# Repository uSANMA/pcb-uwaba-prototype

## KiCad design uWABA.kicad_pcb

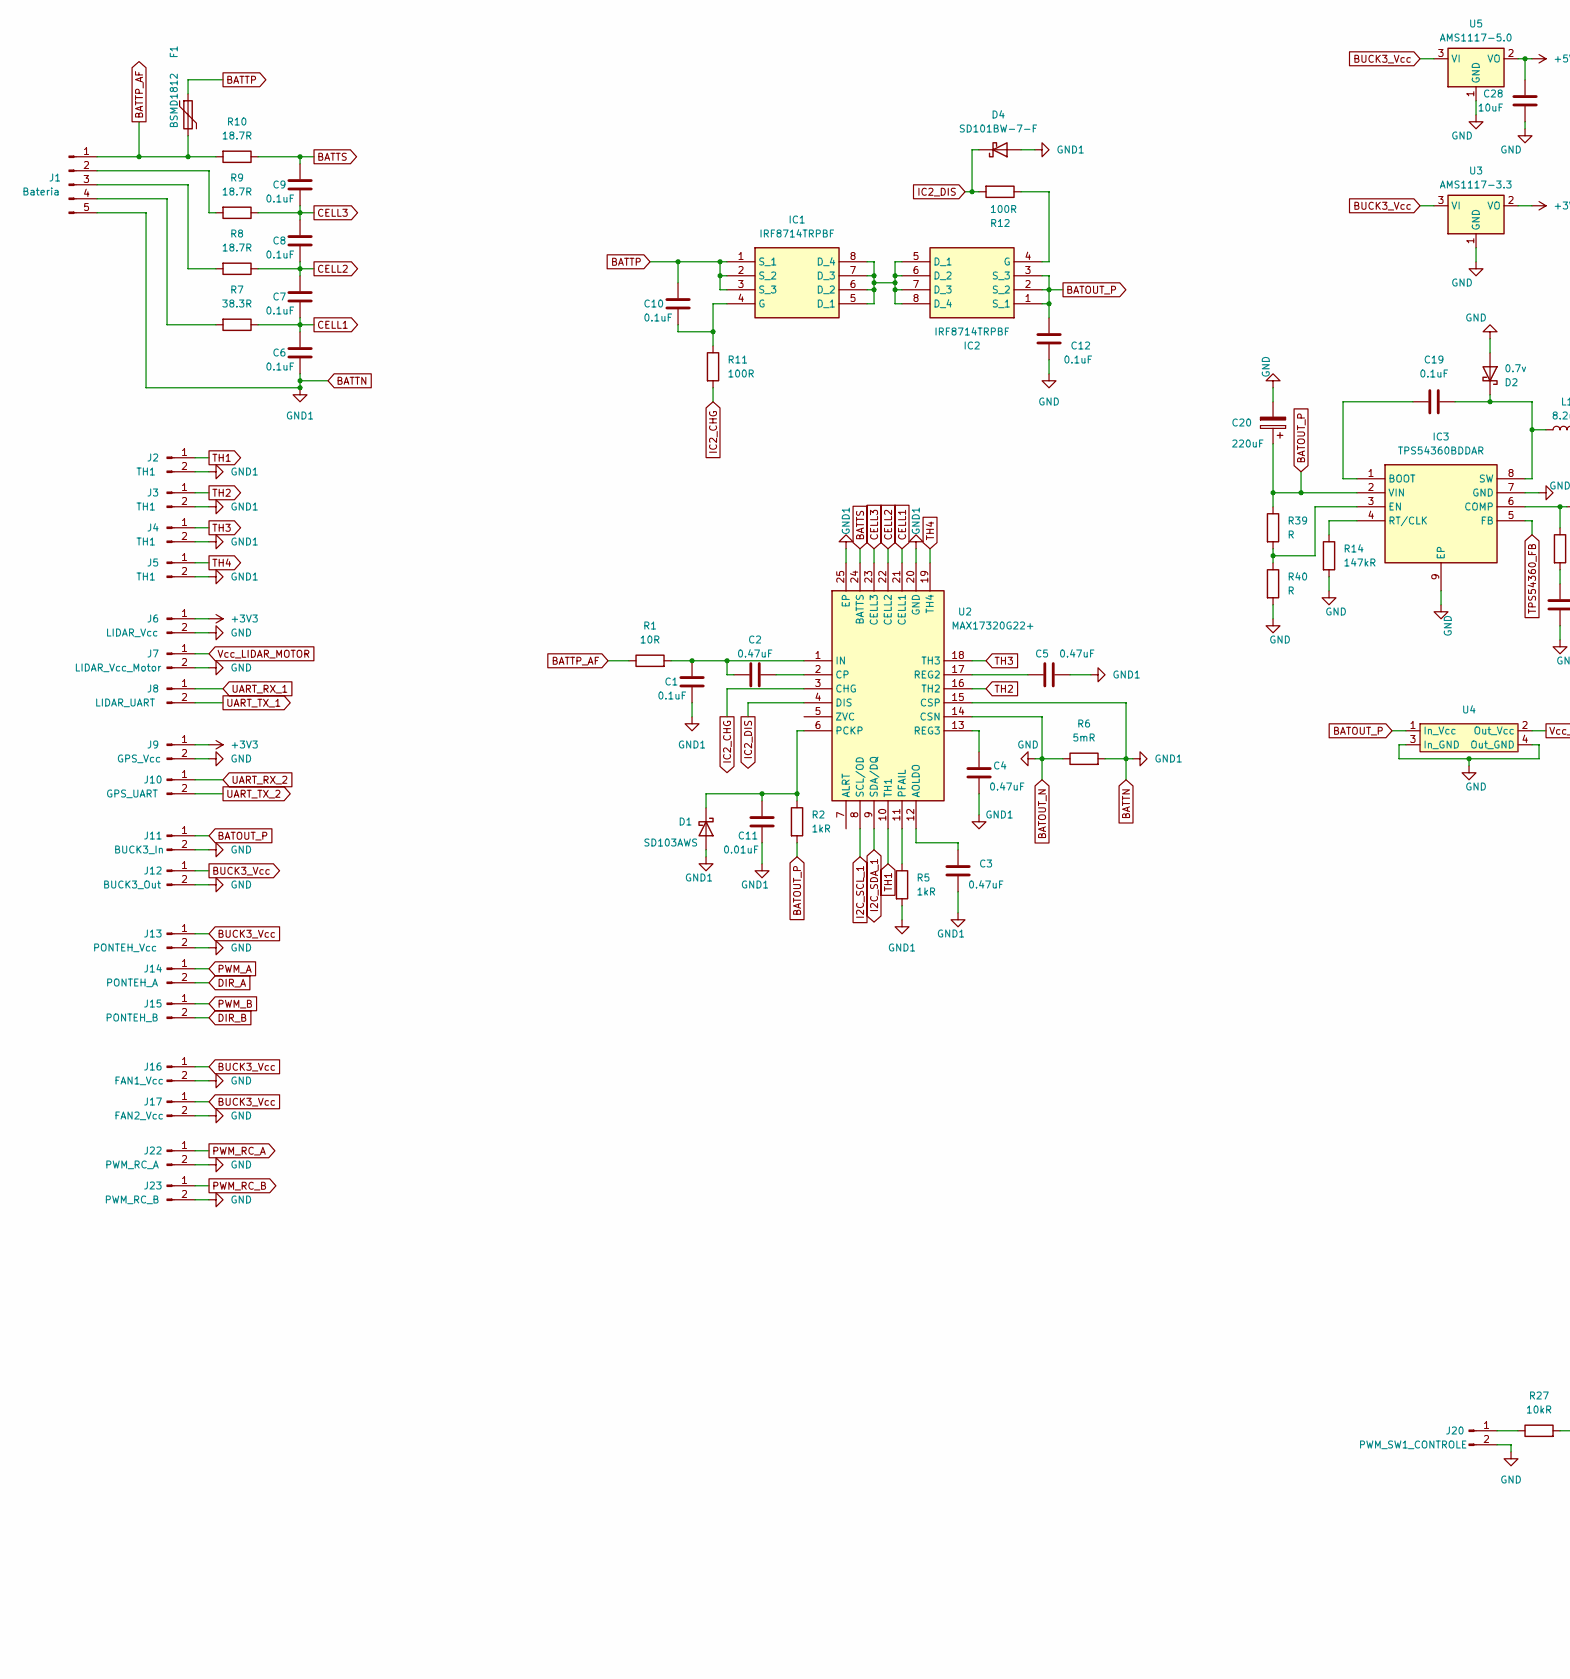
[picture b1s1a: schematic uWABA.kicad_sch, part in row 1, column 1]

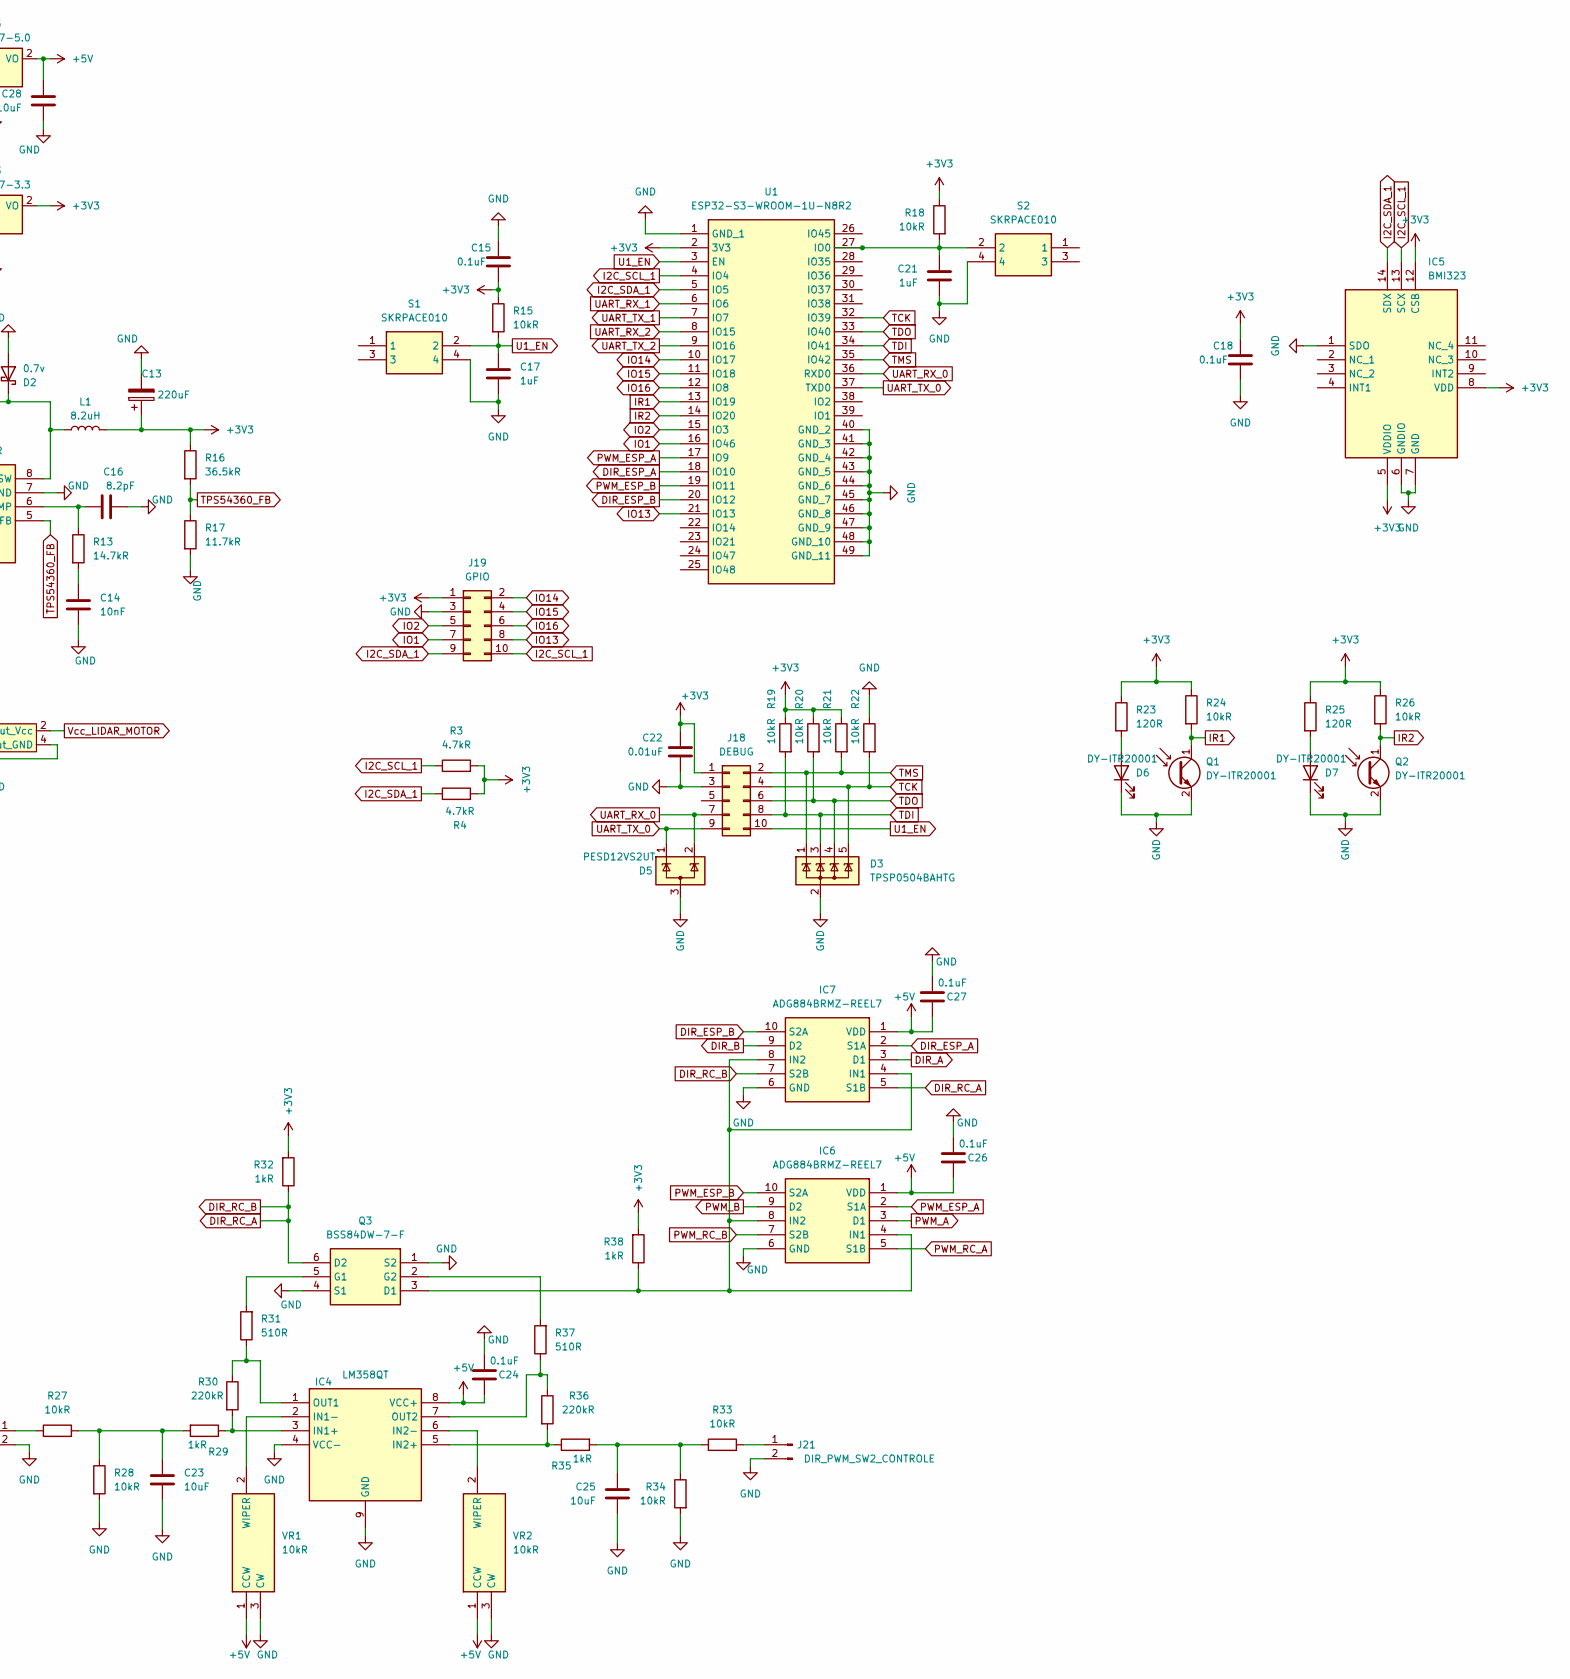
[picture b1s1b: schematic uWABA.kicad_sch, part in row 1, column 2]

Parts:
C1, C6, C7, C8, C9, C10, C12, C15, C18, C19, C24, C26, C27: 0.1uF; C_0805_2012Metric
C2, C3, C4, C5: 0.47uF; C_0603_1608Metric
C11, C22: 0.01uF; C_0603_1608Metric
C13, C20: 220uF; CP_Elec_8x10
C14: 10nF; C_0805_2012Metric
C16: 8.2pF; C_0805_2012Metric
C17, C21: 1uF; C_0805_2012Metric
C23, C25, C28: 10uF; C_0805_2012Metric
D1: SD103AWS; D_SOD-323_HandSoldering
D2: 0.7v; D_SMB
D3: TPSP0504BAHTG; SOT-23-5
D4: SD101BW-7-F; D_SOD-123
D5: PESD12VS2UT; SOT-23
D6, D7: DY-ITR20001; PAD-01x02-2.54mm
F1: BSMD1812; Fuse_1812_4532Metric
IC1, IC2: IRF8714TRPBF; SOIC127P600X175-8N; Mouser Part Number 942-IRF8714TRPBF
IC3: TPS54360BDDAR; SOIC127P600X170-9N; Mouser Part Number 595-TPS54360BDDAR
IC4: LM358QT; SON50P200X200X60-9N-D; Mouser Part Number 511-LM358QT
IC5: BMI323; Mouser Part Number 262-BMI323
IC6, IC7: ADG884BRMZ-REEL7; SOP50P490X110-10N; Mouser Part Number 584-ADG884BRMZ-R7
J1: Bateria; PAD-01x05-Bateria4S
J2, J3, J4, J5: TH1; PAD-01x02-2.54mm
J6: LIDAR_Vcc; PAD-01x02-2.54mm
J7: LIDAR_Vcc_Motor; PAD-01x02-4mm
J8: LIDAR_UART; PAD-01x02-2.54mm
J9: GPS_Vcc; PAD-01x02-2.54mm
J10: GPS_UART; PAD-01x02-2.54mm
J11: BUCK3_In; PAD-01x02-4mm
J12: BUCK3_Out; PAD-01x02-4mm
J13: PONTEH_Vcc; PAD-01x02-4mm
J14: PONTEH_A; PAD-01x02-2.54mm
J15: PONTEH_B; PAD-01x02-2.54mm
J16: FAN1_Vcc; PAD-01x02-2.54mm
J17: FAN2_Vcc; PAD-01x02-2.54mm
J18: DEBUG; PinHeader_2x05_P2.54mm_Vertical_SMD
J19: GPIO; PinHeader_2x05_P2.54mm_Vertical_SMD
J20: PWM_SW1_CONTROLE; PAD-01x02-2.54mm
J21: DIR_PWM_SW2_CONTROLE; PAD-01x02-2.54mm
J22: PWM_RC_A; PAD-01x02-2.54mm
J23: PWM_RC_B; PAD-01x02-2.54mm
L1: 8.2uH; SRN80408R2Y
Q1, Q2: DY-ITR20001; PAD-01x02-2.54mm
Q3: BSS84DW-7-F; SOT65P210X100-6N; Mouser Part Number 621-BSS84DW-F
R1: 10R; R_0805_2012Metric
R2, R5, R29, R32, R35, R38: 1kR; R_0805_2012Metric
R3, R4: 4.7kR; R_0805_2012Metric
R6: 5mR; R_2512_6332Metric
R7: 38.3R; R_1210_3225Metric
R8, R9, R10: 18.7R; R_2512_6332Metric
R11, R12: 100R; R_0805_2012Metric
R13: 14.7kR; R_0805_2012Metric
R14: 147kR; R_0603_1608Metric
R15, R18, R19, R20, R21, R22, R24, R26, R27, R28, R33, R34: 10kR; R_0805_2012Metric
R16: 36.5kR; R_0805_2012Metric
R17: 11.7kR; R_0805_2012Metric
R23, R25: 120R; R_0805_2012Metric
R30, R36: 220kR; R_0805_2012Metric
R31, R37: 510R; R_0805_2012Metric
R39, R40: R; R_0805_2012Metric
S1, S2: SKRPACE010; SMT(4.2X3.2); Mouser Part Number 688-SKRPACE010
U1: ESP32-S3-WROOM-1U-N8R2; ESP32S3WROOM1UN8R2; Mouser Part Number 356-ESP32S3WRM1UN8R2
U2: MAX17320G22+; QFN50P400X400X80-25N; Mouser Part Number 700-MAX17320G22+
U3: AMS1117-3.3; SOT-223-3_TabPin2
U4: LM2596-Modulo
U5: AMS1117-5.0; SOT-223-3_TabPin2
VR1, VR2: 10kR; 3266W1103; Mouser Part Number 652-3266W-1-103

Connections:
+3V3: C13.1, C15.2, C18.1, C22.1, IC5.5 (VDDIO), IC5.8 (VDD), IC5.12 (CSB), J6.1, J9.1, J18.1, J19.1, L1.2, R3.2, R4.2, R15.1, R16.1, R18.1, R19.1, R20.1, R21.1, R23.1, R24.1, R25.1, R26.1, R32.2, R38.2, U1.2 (3V3), U3.2 (VO)
+5V: C24.1, C26.1, C27.1, C28.1, IC4.8 (VCC+), IC6.1 (VDD), IC7.1 (VDD), U5.2 (VO), VR1.1 (CCW), VR2.1 (CCW)
BATOUT_N: C12.2, C13.2, C14.2, C15.1, C16.2, C17.2, C18.2, C20.2, C21.2, C22.2, C23.2, C24.2, C25.2, C26.2, C27.2, C28.2, D2.2 (A), D3.2 (A), D5.3 (A), D6.1 (K), D7.1 (K), IC3.7 (GND), IC3.9 (EP), IC4.4 (VCC-), IC4.9 (GND), IC5.1 (SDO), IC5.6 (GNDIO), IC5.7 (GND), IC6.6 (GND), IC7.6 (GND), J6.2, J7.2, J9.2, J11.2, J12.2, J13.2, J16.2, J17.2, J18.3, J19.3, J20.2, J21.2, J22.2, J23.2, Q1.2 (E), Q2.2 (E), Q3.1 (S2), Q3.4 (S1), R6.1, R14.2, R17.2, R22.1, R28.2, R34.2, R40.2, S1.4, S2.4, U1.1 (GND_1), U1.40 (GND_2), U1.41 (GND_3), U1.42 (GND_4), U1.43 (GND_5), U1.44 (GND_6), U1.45 (GND_7), U1.46 (GND_8), U1.47 (GND_9), U1.48 (GND_10), U1.49 (GND_11), U2.14 (CSN), U3.1 (GND), U4.3 (In_GND), U4.4 (Out_GND), U5.1 (GND), VR1.3 (CW), VR2.3 (CW)
BATOUT_P: C12.1, C20.1, IC2.1 (S_1), IC2.2 (S_2), IC2.3 (S_3), IC3.2 (VIN), J11.1, R2.2, R39.1, U4.1 (In_Vcc)
BATTN: C1.2, C3.1, C4.2, C5.2, C6.2, C11.2, D1.2 (A), D4.2 (A), J1.5, J2.2, J3.2, J4.2, J5.2, R5.2, R6.2, U2.15 (CSP), U2.20 (GND), U2.25 (EP)
BATTP: C10.1, F1.1, IC1.1 (S_1), IC1.2 (S_2), IC1.3 (S_3)
BATTP_AF: F1.2, J1.1, R1.1, R10.2
BATTS: C9.1, R10.1, U2.24 (BATTS)
BUCK3_Vcc: J12.1, J13.1, J16.1, J17.1, U3.3 (VI), U5.3 (VI)
CELL1: C6.1, C7.2, R7.1, U2.21 (CELL1)
CELL2: C7.1, C8.2, R8.1, U2.22 (CELL2)
CELL3: C8.1, C9.2, R9.1, U2.23 (CELL3)
DIR_A: IC7.3 (D1), J14.2
DIR_B: IC7.9 (D2), J15.2
DIR_ESP_A: IC7.2 (S1A), U1.18 (IO10)
DIR_ESP_B: IC7.10 (S2A), U1.20 (IO12)
DIR_RC_A: IC7.5 (S1B), IC7.7 (S2B), Q3.6 (D2), R32.1
I2C_SCL_1: IC5.13 (SCX), J19.10, R3.1, U1.4 (IO4), U2.8 (SCL/OD)
I2C_SDA_1: IC5.14 (SDX), J19.9, R4.1, U1.5 (IO5), U2.9 (SDA/DQ)
IC2_CHG: R11.2, U2.3 (CHG)
IC2_DIS: D4.1 (K), R12.2, U2.4 (DIS)
IO1: J19.7, U1.16 (IO46)
IO2: J19.5, U1.15 (IO3)
IO13: J19.8, U1.21 (IO13)
IO14: J19.2, U1.10 (IO17)
IO15: J19.4, U1.11 (IO18)
IO16: J19.6, U1.12 (IO8)
IR1: Q1.1 (C), R24.2, U1.13 (IO19)
IR2: Q2.1 (C), R26.2, U1.14 (IO20)
unnamed: C14.1, R13.2
unnamed: C23.1, R27.2, R28.1, R29.2
unnamed: C25.1, R33.2, R34.1, R35.2
unnamed: C11.1, D1.1 (K), R2.1, U2.6 (PCKP)
unnamed: C19.1, D2.1 (K), IC3.8 (SW), L1.1
unnamed: D6.2 (A), R23.2
unnamed: D7.2 (A), R25.2
unnamed: IC1.5 (D_1), IC1.6 (D_2), IC1.7 (D_3), IC1.8 (D_4), IC2.5 (D_1), IC2.6 (D_2), IC2.7 (D_3), IC2.8 (D_4)
unnamed: C10.2, IC1.4 (G), R11.1
unnamed: IC2.4 (G), R12.1
unnamed: C19.2, IC3.1 (BOOT)
unnamed: C16.1, IC3.6 (COMP), R13.1
unnamed: IC3.3 (EN), R39.2, R40.1
unnamed: IC3.4 (RT/CLK), R14.1
unnamed: IC4.3 (IN1+), R29.1, R30.2
unnamed: IC4.2 (IN1-), VR1.2 (WIPER)
unnamed: IC4.5 (IN2+), R35.1, R36.2
unnamed: IC4.6 (IN2-), VR2.2 (WIPER)
unnamed: IC4.1 (OUT1), R30.1, R31.1
unnamed: IC4.7 (OUT2), R36.1, R37.1
unnamed: IC6.4 (IN1), IC6.8 (IN2), IC7.4 (IN1), IC7.8 (IN2), Q3.3 (D1), R38.1
unnamed: J1.2, R9.2
unnamed: J1.3, R8.2
unnamed: J1.4, R7.2
unnamed: J20.1, R27.1
unnamed: J21.1, R33.1
unnamed: Q3.5 (G1), R31.2
unnamed: Q3.2 (G2), R37.2
unnamed: C21.1, R18.2, S2.2, U1.27 (IO0)
unnamed: C3.2, U2.12 (AOLDO)
unnamed: C2.2, U2.2 (CP)
unnamed: C1.1, C2.1, R1.2, U2.1 (IN)
unnamed: R5.1, U2.11 (PFAIL)
unnamed: C5.1, U2.17 (REG2)
unnamed: C4.1, U2.13 (REG3)
PWM_A: IC6.3 (D1), J14.1
PWM_B: IC6.9 (D2), J15.1
PWM_ESP_A: IC6.2 (S1A), U1.17 (IO9)
PWM_ESP_B: IC6.10 (S2A), U1.19 (IO11)
PWM_RC_A: IC6.5 (S1B), J22.1
PWM_RC_B: IC6.7 (S2B), J23.1
TCK: D3.5 (K), J18.4, R22.2, U1.32 (IO39)
TDI: D3.3 (K), J18.8, R19.2, U1.34 (IO41)
TDO: D3.4 (K), J18.6, R20.2, U1.33 (IO40)
TH1: J2.1, U2.10 (TH1)
TH2: J3.1, U2.16 (TH2)
TH3: J4.1, U2.18 (TH3)
TH4: J5.1, U2.19 (TH4)
TMS: D3.1 (K), J18.2, R21.2, U1.35 (IO42)
TPS54360_FB: IC3.5 (FB), R16.2, R17.1
U1_EN: C17.1, J18.10, R15.2, S1.2, U1.3 (EN)
UART_RX_0: D5.2 (K), J18.7, U1.36 (RXD0)
UART_RX_1: J8.1, U1.6 (IO6)
UART_RX_2: J10.1, U1.8 (IO15)
UART_TX_0: D5.1 (K), J18.9, U1.37 (TXD0)
UART_TX_1: J8.2, U1.7 (IO7)
UART_TX_2: J10.2, U1.9 (IO16)
Vcc_LIDAR_MOTOR: J7.1, U4.2 (Out_Vcc)

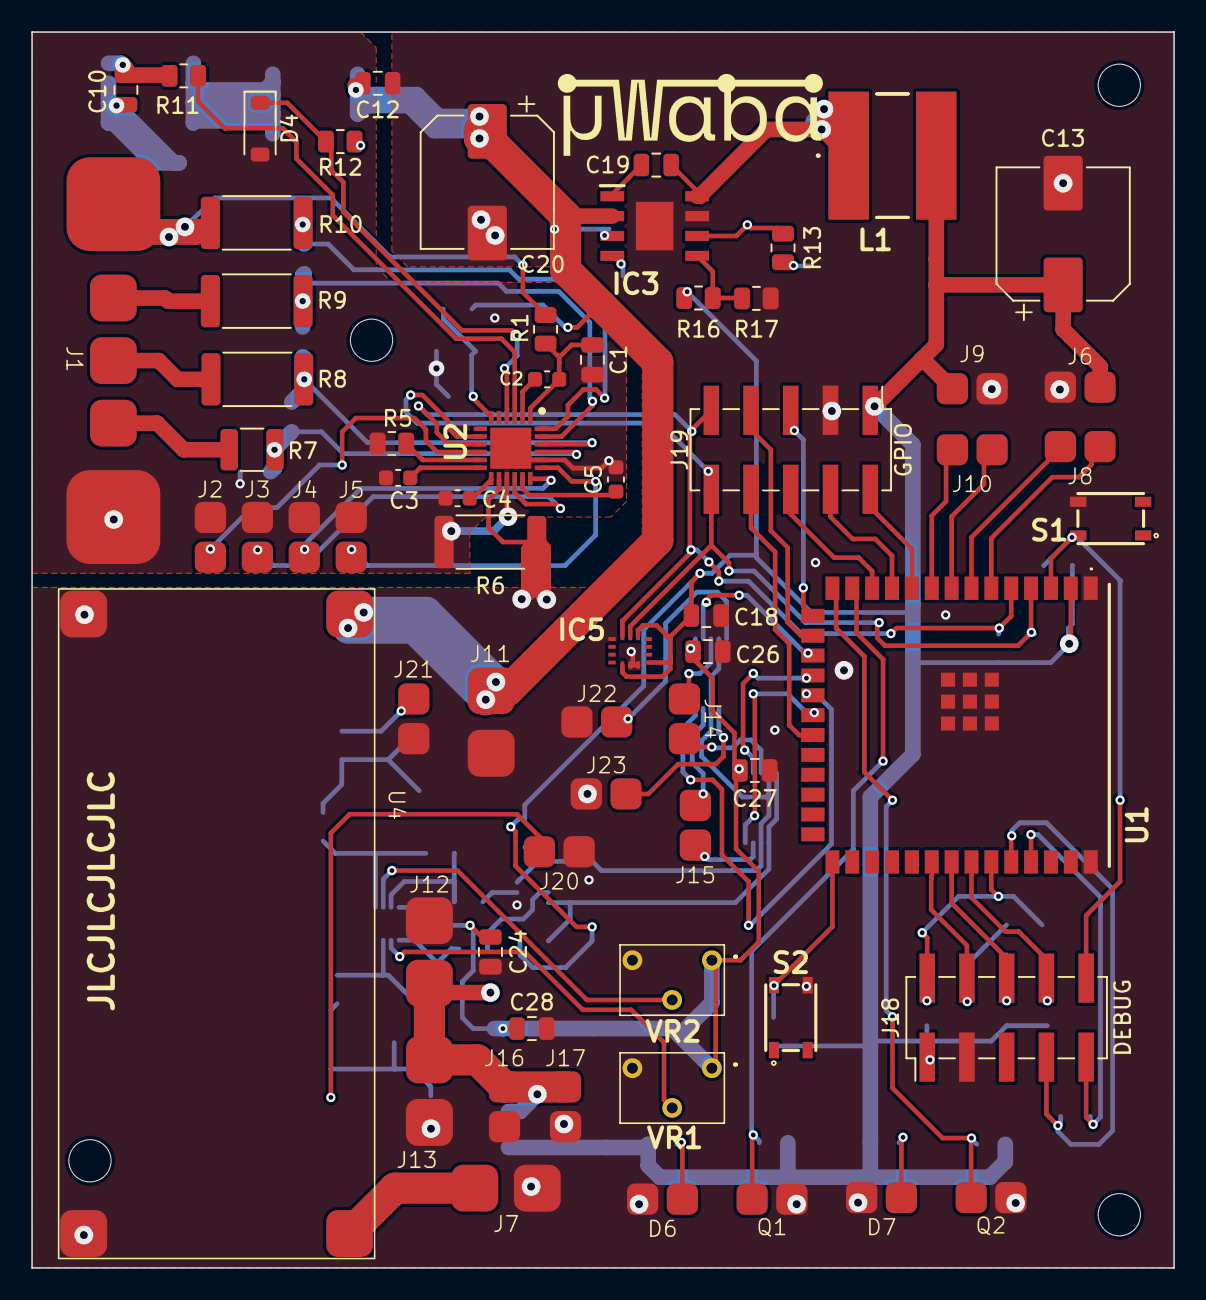
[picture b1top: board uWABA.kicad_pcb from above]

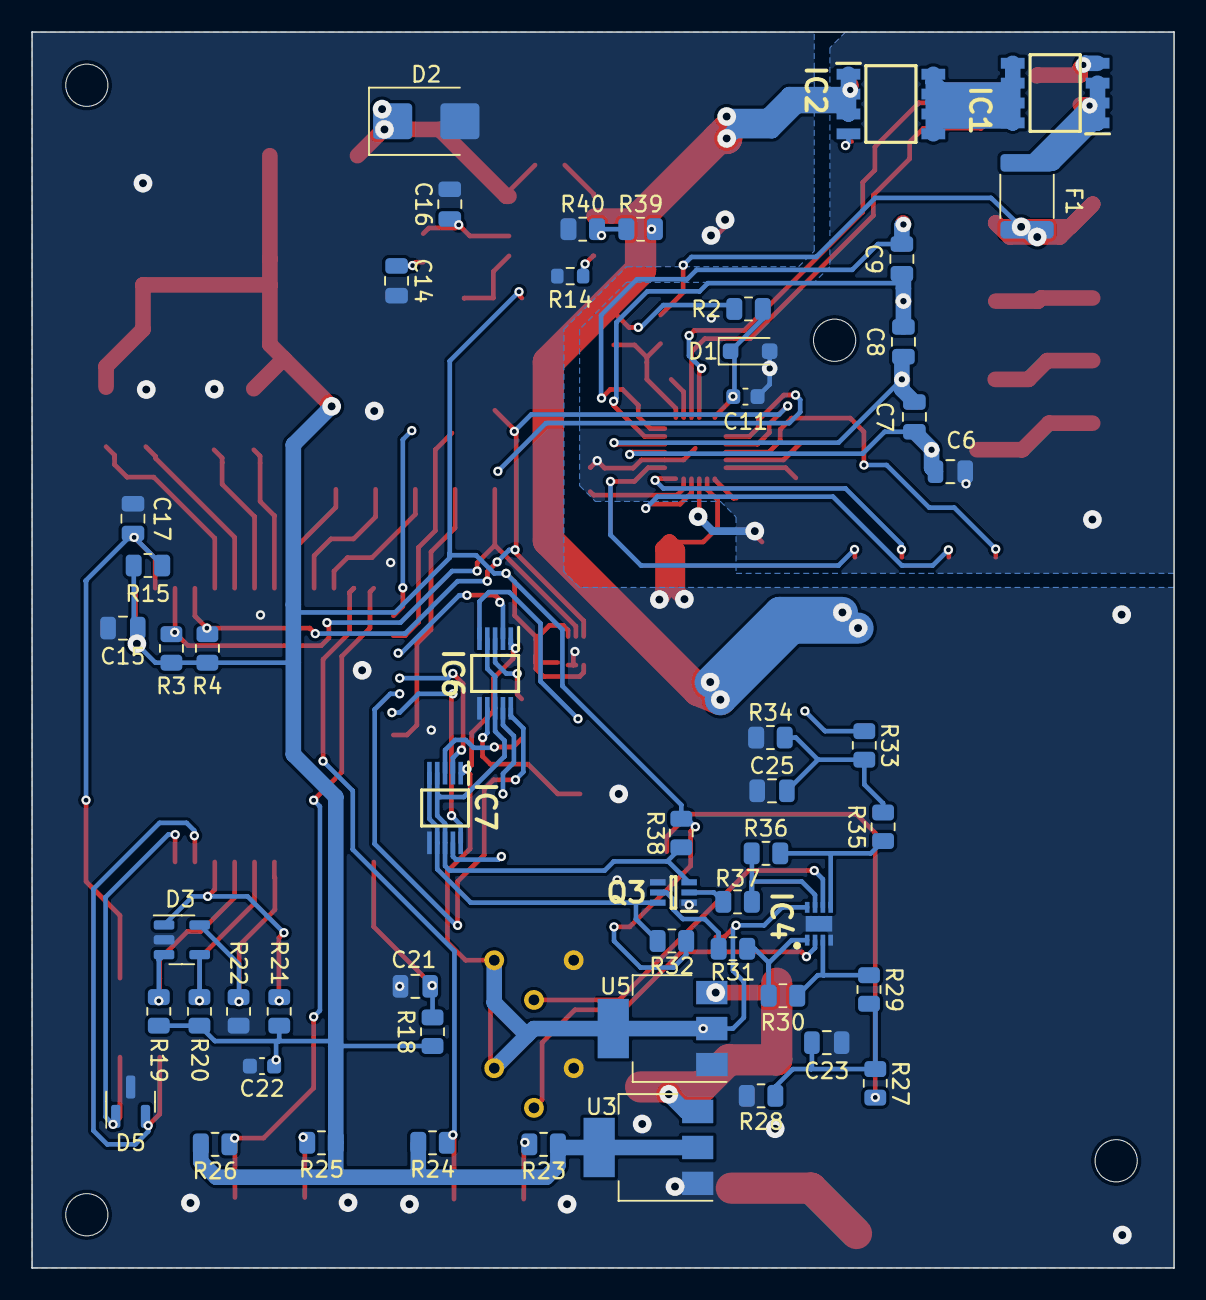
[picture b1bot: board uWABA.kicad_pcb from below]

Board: 2 copper layers, 73.0 x 79.0 mm, 119 parts (54 on the bottom side), 87 nets.

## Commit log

2024-03-06 v1.0
